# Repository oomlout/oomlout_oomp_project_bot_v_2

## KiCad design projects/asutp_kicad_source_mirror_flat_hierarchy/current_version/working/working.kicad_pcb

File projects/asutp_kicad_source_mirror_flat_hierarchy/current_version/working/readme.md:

# kicad_source_mirror
 
## summary 
* id: asutp_kicad_source_mirror_flat_hierarchy
* user: asutp
* name: kicad_source_mirror
* board: flat_hierarchy
* repo: https://github.com/asutp/kicad-source-mirror
* src_file_repo_kicad_pcb: demos/flat_hierarchy/flat_hierarchy.kicad_pcb
* src_file_repo_kicad_pcb_link: https://github.com/asutp/kicad-source-mirror/tree/master/demos/flat_hierarchy/flat_hierarchy.kicad_pcb

* src_file_repo_sch: demos/flat_hierarchy/flat_hierarchy.sch
* src_file_repo_sch_link: https://github.com/asutp/kicad-source-mirror/tree/master/demos/flat_hierarchy/flat_hierarchy.sch
* full details link: https://github.com/oomlout/oomlout_oomp_project_bot_v_2/tree/main/projects/asutp_kicad_source_mirror_flat_hierarchy/current_version/working  

## pcb  

[board (pdf)](working.pdf)  

## working_bom
| Id | Designator | Footprint | Quantity | Designation | Supplier and ref |  | None | 
| --- | --- | --- | --- | --- | --- | --- | --- | 
| 1 | P3 | 40DIP-ELL600 | 1 | SUPP40 |  |  | [''] | 
| 2 | 1PIN,1PIN,1PIN,1PIN,1PIN,1PIN | 1pin | 6 | P*** |  |  | [''] | 
| 3 | P2 | 28DIP-ELL300 | 1 | SUPP28 |  |  | [''] | 
| 4 | C1 | CP10 | 1 | 100uF |  |  | [''] | 
| 5 | C2 | CP10 | 1 | 220uF |  |  | [''] | 
| 6 | C3 | CP8 | 1 | 22uF/25V |  |  | [''] | 
| 7 | C4 | C1-1 | 1 | 0 |  |  | [''] | 
| 8 | C5 | C1-1 | 1 | 10nF |  |  | [''] | 
| 9 | C6,C7,C8 | C1-1 | 3 | 100nF |  |  | [''] | 
| 10 | C9 | C1-1 | 1 | 22OnF |  |  | [''] | 
| 11 | D1 | D5 | 1 | 1N4004 |  |  | [''] | 
| 12 | D2,D3,D4,D5,D6,D7,D11 | D3 | 7 | BAT43 |  |  | [''] | 
| 13 | D8 | LEDV | 1 | RED-LED |  |  | [''] | 
| 14 | D9 | LEDV | 1 | GREEN-LED |  |  | [''] | 
| 15 | D10 | D5 | 1 | SCHOTTKY |  |  | [''] | 
| 16 | D12 | LEDV | 1 | YELLOW-LED |  |  | [''] | 
| 17 | J1 | DB9FC | 1 | DB9-FEMAL |  |  | [''] | 
| 18 | JP1 | PIN_ARRAY_2X1 | 1 | JUMPER |  |  | [''] | 
| 19 | L1 | INDUCTOR_V | 1 | 22uH |  |  | [''] | 
| 20 | P1 | bornier2 | 1 | CONN_2 |  |  | [''] | 
| 21 | Q1 | TO92 | 1 | BC237 |  |  | [''] | 
| 22 | Q2,Q3 | TO92 | 2 | BC307 |  |  | [''] | 
| 23 | R1,R2,R3,R4,R5,R6,R7 | R4 | 7 | 10K |  |  | [''] | 
| 24 | R8 | R4 | 1 | 1K |  |  | [''] | 
| 25 | R9,R19,R20 | R4 | 3 | 2.2K |  |  | [''] | 
| 26 | R10 | R4 | 1 | 5,1K |  |  | [''] | 
| 27 | R11,R17 | R4 | 2 | 22K |  |  | [''] | 
| 28 | R12,R13,R14,R21 | R4 | 4 | 470 |  |  | [''] | 
| 29 | R15 | R4 | 1 | 6.2K |  |  | [''] | 
| 30 | R16 | R4 | 1 | 62K |  |  | [''] | 
| 31 | R18 | R4 | 1 | 220 |  |  | [''] | 
| 32 | RV1 | RV2X4 | 1 | 1K |  |  | [''] | 
| 33 | U1 | DIP-8__300_ELL | 1 | 24Cxx |  |  | [''] | 
| 34 | U2 | DIP-14__300_ELL | 1 | 74HC125 |  |  | [''] | 
| 35 | U3 | LM78XX | 1 | 7805 |  |  | [''] | 
| 36 | U4 | DIP-8__300_ELL | 1 | LT1373 |  |  | [''] | 
| 37 | U5 | DIP-18__300_ELL | 1 | PIC_18_PINS |  |  | [''] | 
| 38 | U6 | DIP-8__300_ELL | 1 | PIC_8_PINS |  |  | [''] |

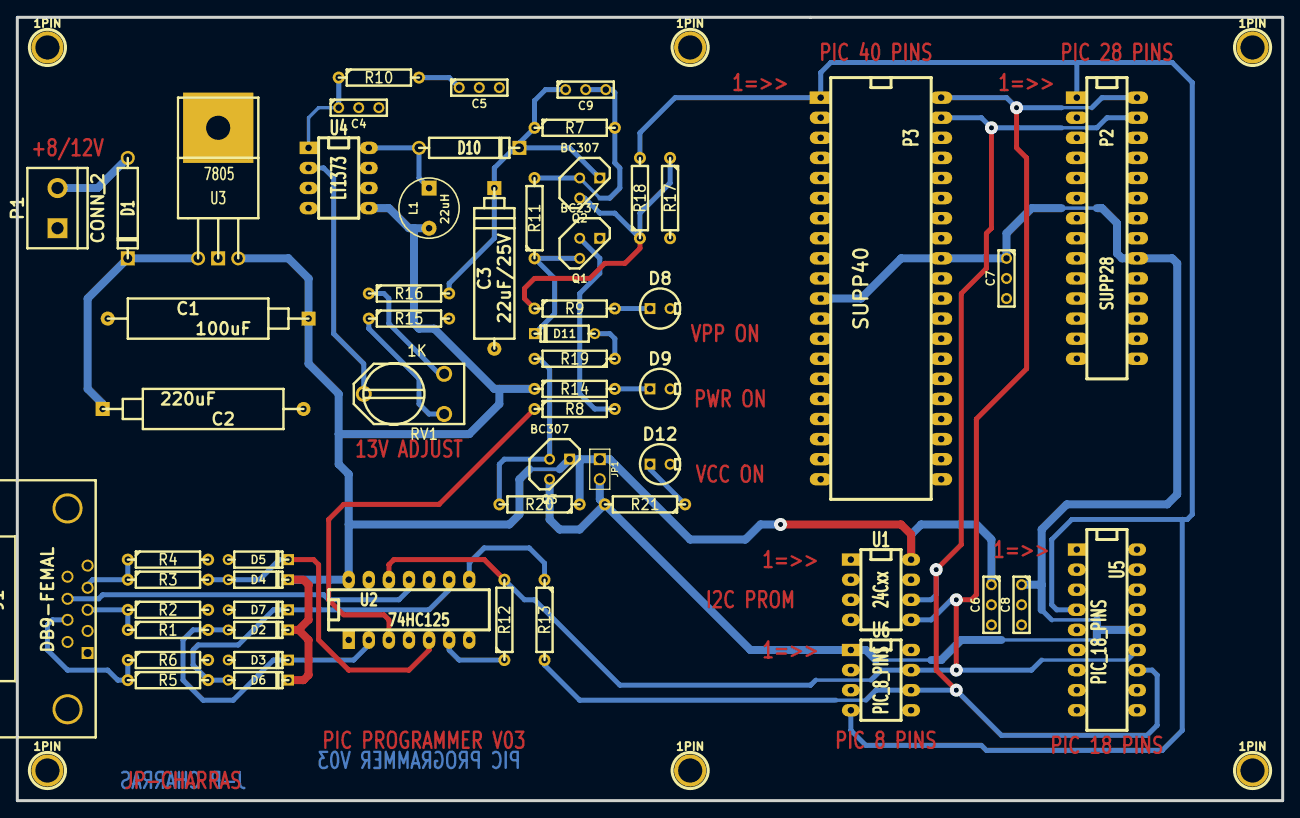
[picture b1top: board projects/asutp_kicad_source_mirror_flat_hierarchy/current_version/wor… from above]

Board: 2 copper layers, 160.0 x 99.1 mm, 64 parts (0 on the bottom side), 34 nets.

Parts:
1PIN, 1PIN#2, 1PIN#3, 1PIN#4, 1PIN#5, 1PIN#6: P***; 1pin
C1: 100uF; CP10
C2: 220uF; CP10
C3: 22uF/25V; CP8
C4: 0; C1-1
C5: 10nF; C1-1
C6, C7, C8: 100nF; C1-1
C9: 22OnF; C1-1
D1: 1N4004; D5
D2, D3, D4, D5, D6, D7, D11: BAT43; D3
D8: RED-LED; LEDV
D9: GREEN-LED; LEDV
D10: SCHOTTKY; D5
D12: YELLOW-LED; LEDV
J1: DB9-FEMAL; DB9FC
JP1: JUMPER; PIN_ARRAY_2X1
L1: 22uH; INDUCTOR_V
P1: CONN_2; bornier2
P2: SUPP28; 28DIP-ELL300
P3: SUPP40; 40DIP-ELL600
Q1: BC237; TO92
Q2, Q3: BC307; TO92
R1, R2, R3, R4, R5, R6, R7: 10K; R4
R8: 1K; R4
R9, R19, R20: 2.2K; R4
R10: 5,1K; R4
R11, R17: 22K; R4
R12, R13, R14, R21: 470; R4
R15: 6.2K; R4
R16: 62K; R4
R18: 220; R4
RV1: 1K; RV2X4
U1: 24Cxx; DIP-8__300_ELL
U2: 74HC125; DIP-14__300_ELL
U3: 7805; LM78XX
U4: LT1373; DIP-8__300_ELL
U5: PIC_18_PINS; DIP-18__300_ELL
U6: PIC_8_PINS; DIP-8__300_ELL

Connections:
/pic_programmer/CTS: J1.8, U2.11
/pic_programmer/DTR: J1.4, R3.1, R4.1
/pic_programmer/PC-CLOCK-OUT: J1.7, R5.1, R6.1
/pic_programmer/TXD: J1.3, R1.1, R2.1
CLOCK-RB6: P2.27, P3.39, R13.2, U1.6, U5.12, U6.6
DATA-RB7: P2.28, P3.40, R12.2, U1.5, U2.12, U5.13, U6.7
GND: C1.2, C2.2, C3.2, C4.2, C5.2, C6.2, C7.2, C8.2, D3.1, D5.1, D7.1, D8.2, D9.2, D12.2, J1.5, P1.1, P2.8, P2.19, P3.8, P3.12, P3.31, Q1.1, R2.2, R4.2, R6.2, R15.2, R17.2, U1.1, U1.2, U1.3, U1.4, U2.1, U2.4, U2.7, U2.10, U2.13, U3.GND, U4.6, U4.7, U5.5, U6.8
unnamed: C2.1, D1.2, U3.VI
unnamed: C4.1, R10.1, U4.1
unnamed: C5.1, R10.2
unnamed: C9.2, Q2.2, R7.2, R11.2
unnamed: D1.1, P1.2
unnamed: D2.1, D3.2, R1.2, U2.2
unnamed: D4.1, D5.2, R3.2, U2.5
unnamed: D6.1, D7.2, R5.2, U2.9
unnamed: D8.1, R9.2
unnamed: D9.1, R14.2
unnamed: D10.1, L1.1, U4.8
unnamed: D11.1, R19.1
unnamed: D11.2, Q1.3, R11.1
unnamed: D12.1, R21.1
unnamed: Q1.2, R8.2
unnamed: Q2.3, R9.1, R17.1, R18.1
unnamed: Q3.2, R19.2, R20.2
unnamed: R8.1, U2.3
unnamed: R12.1, U2.6
unnamed: R13.1, U2.8
unnamed: R15.1, RV1.1
unnamed: R16.1, RV1.3
unnamed: RV1.2, U4.2
VCC: C1.1, C6.1, D2.2, D4.2, D6.2, JP1.1, L1.2, Q3.1, R14.1, R20.1, U1.8, U2.14, U3.VO, U4.5
VCC_PIC: C7.1, C8.1, JP1.2, P2.20, P3.11, P3.32, Q3.3, R21.2, U5.14, U6.1
VPP: C3.1, C9.1, D10.2, Q2.1, R7.1, R16.2
VPP-MCLR: P2.1, P3.1, R18.2, U5.4, U6.4

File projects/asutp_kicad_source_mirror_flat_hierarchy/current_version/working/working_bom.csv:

"Id";"Designator";"Footprint";"Quantity";"Designation";"Supplier and ref";
1;"P3";"40DIP-ELL600";1;"SUPP40";;;
2;"1PIN,1PIN,1PIN,1PIN,1PIN,1PIN";"1pin";6;"P***";;;
3;"P2";"28DIP-ELL300";1;"SUPP28";;;
4;"C1";"CP10";1;"100uF";;;
5;"C2";"CP10";1;"220uF";;;
6;"C3";"CP8";1;"22uF/25V";;;
7;"C4";"C1-1";1;"0";;;
8;"C5";"C1-1";1;"10nF";;;
9;"C6,C7,C8";"C1-1";3;"100nF";;;
10;"C9";"C1-1";1;"22OnF";;;
11;"D1";"D5";1;"1N4004";;;
12;"D2,D3,D4,D5,D6,D7,D11";"D3";7;"BAT43";;;
13;"D8";"LEDV";1;"RED-LED";;;
14;"D9";"LEDV";1;"GREEN-LED";;;
15;"D10";"D5";1;"SCHOTTKY";;;
16;"D12";"LEDV";1;"YELLOW-LED";;;
17;"J1";"DB9FC";1;"DB9-FEMAL";;;
18;"JP1";"PIN_ARRAY_2X1";1;"JUMPER";;;
19;"L1";"INDUCTOR_V";1;"22uH";;;
20;"P1";"bornier2";1;"CONN_2";;;
21;"Q1";"TO92";1;"BC237";;;
22;"Q2,Q3";"TO92";2;"BC307";;;
23;"R1,R2,R3,R4,R5,R6,R7";"R4";7;"10K";;;
24;"R8";"R4";1;"1K";;;
25;"R9,R19,R20";"R4";3;"2.2K";;;
26;"R10";"R4";1;"5,1K";;;
27;"R11,R17";"R4";2;"22K";;;
28;"R12,R13,R14,R21";"R4";4;"470";;;
29;"R15";"R4";1;"6.2K";;;
30;"R16";"R4";1;"62K";;;
31;"R18";"R4";1;"220";;;
32;"RV1";"RV2X4";1;"1K";;;
33;"U1";"DIP-8__300_ELL";1;"24Cxx";;;
34;"U2";"DIP-14__300_ELL";1;"74HC125";;;
35;"U3";"LM78XX";1;"7805";;;
36;"U4";"DIP-8__300_ELL";1;"LT1373";;;
37;"U5";"DIP-18__300_ELL";1;"PIC_18_PINS";;;
38;"U6";"DIP-8__300_ELL";1;"PIC_8_PINS";;;

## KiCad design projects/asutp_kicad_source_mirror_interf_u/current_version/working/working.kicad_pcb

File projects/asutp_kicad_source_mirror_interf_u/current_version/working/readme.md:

# kicad_source_mirror
 
## summary 
* id: asutp_kicad_source_mirror_interf_u
* user: asutp
* name: kicad_source_mirror
* board: interf_u
* repo: https://github.com/asutp/kicad-source-mirror
* src_file_repo_kicad_pcb: demos/interf_u/interf_u.kicad_pcb
* src_file_repo_kicad_pcb_link: https://github.com/asutp/kicad-source-mirror/tree/master/demos/interf_u/interf_u.kicad_pcb

* src_file_repo_sch: demos/interf_u/interf_u.sch
* src_file_repo_sch_link: https://github.com/asutp/kicad-source-mirror/tree/master/demos/interf_u/interf_u.sch
* full details link: https://github.com/oomlout/oomlout_oomp_project_bot_v_2/tree/main/projects/asutp_kicad_source_mirror_interf_u/current_version/working  

## schematic  
  
[schematic (pdf)](working_schematic.pdf) 

## pcb  

[board (pdf)](working.pdf)  

## working_bom
| Id | Designator | Footprint | Quantity | Designation | Supplier and ref |  | None | 
| --- | --- | --- | --- | --- | --- | --- | --- | 
| 1 | BUS1 | BUS_PC | 1 | BUSPC |  |  | [''] | 
| 2 | R4,R5 | R3 | 2 | 330 |  |  | [''] | 
| 3 | D1,D2 | LED-5MM | 2 | LED |  |  | [''] | 
| 4 | U9 | PGA120 | 1 | 4003APG120 |  |  | [''] | 
| 5 | C6,C5,C4,C1 | CP6 | 4 | 47uF |  |  | [''] | 
| 6 | R1 | R3 | 1 | 100K |  |  | [''] | 
| 7 | R2 | R3 | 1 | 1K |  |  | [''] | 
| 8 | X1 | HC-18UH | 1 | 8MHz |  |  | [''] | 
| 9 | C2,C3 | C_Disc_D3_P2.5 | 2 | 47pF |  |  | [''] | 
| 10 | U5 | DIP-32__600 | 1 | 628128 |  |  | [''] | 
| 11 | R3 | R3 | 1 | 10K |  |  | [''] | 
| 12 | P1 | DB25FC | 1 | DB25FEMELLE |  |  | [''] | 
| 13 | RR1 | r_pack9 | 1 | 9x1K |  |  | [''] | 
| 14 | JP1 | Pin_Header_Straight_2x08 | 1 | CONN_8X2 |  |  | [''] | 
| 15 | U1 | DIP-20__300 | 1 | 74LS245 |  |  | [''] | 
| 16 | U2 | DIP-20__300 | 1 | 74LS688 |  |  | [''] | 
| 17 | U3 | DIP-20__300 | 1 | 74LS541 |  |  | [''] | 
| 18 | U8 | DIP-24__300 | 1 | EP600 |  |  | [''] | 
| 19 | G*** | LOGO | 1 | LOGO |  |  | [''] | 

## bom_schematic
| Ref | Qnty | Value | Cmp name | Footprint | Description | Vendor | DNP | 
| --- | --- | --- | --- | --- | --- | --- | --- | 
| BUS1 | 1 | BUSPC | BUSPC | BUS_PC |  |  |  | 
| C1, C4, C5, C6 | 4 | 47uF | CP | Discret:CP6 |  |  |  | 
| C2, C3 | 2 | 47pF | C | Discret:C1 |  |  |  | 
| D1, D2 | 2 | LED | LED | LEDs:LED-5MM |  |  |  | 
| JP1 | 1 | CONN_8X2 | CONN_8X2 | pin_array_8x2 |  |  |  | 
| P1 | 1 | DB25FEMELLE | DB25 | connect:DB25FC |  |  |  | 
| R1 | 1 | 100K | R | Discret:R3 |  |  |  | 
| R2 | 1 | 1K | R | Discret:R3 |  |  |  | 
| R3 | 1 | 10K | R | Discret:R3 |  |  |  | 
| R4, R5 | 2 | 330 | R | Discret:R3 |  |  |  | 
| RR1 | 1 | 9x1K | RR9 | Discret:r_pack9 |  |  |  | 
| U1 | 1 | 74LS245 | 74LS245 | Dip_sockets:DIP-20__300 |  |  |  | 
| U2 | 1 | 74LS688 | 74LS688 | Dip_sockets:DIP-20__300 |  |  |  | 
| U3 | 1 | 74LS541 | 74LS541 | Dip_sockets:DIP-20__300 |  |  |  | 
| U5 | 1 | 628128 | 628128 | Dip_sockets:DIP-32__600 |  |  |  | 
| U8 | 1 | EP600 | EP600 | Dip_sockets:DIP-24__300 |  |  |  | 
| U9 | 1 | 4003APG120 | 4003APG120 | Sockets_PGA:PGA120 |  |  |  | 
| X1 | 1 | 8MHz | CRYSTAL | Discret:HC-18UH |  |  |  |

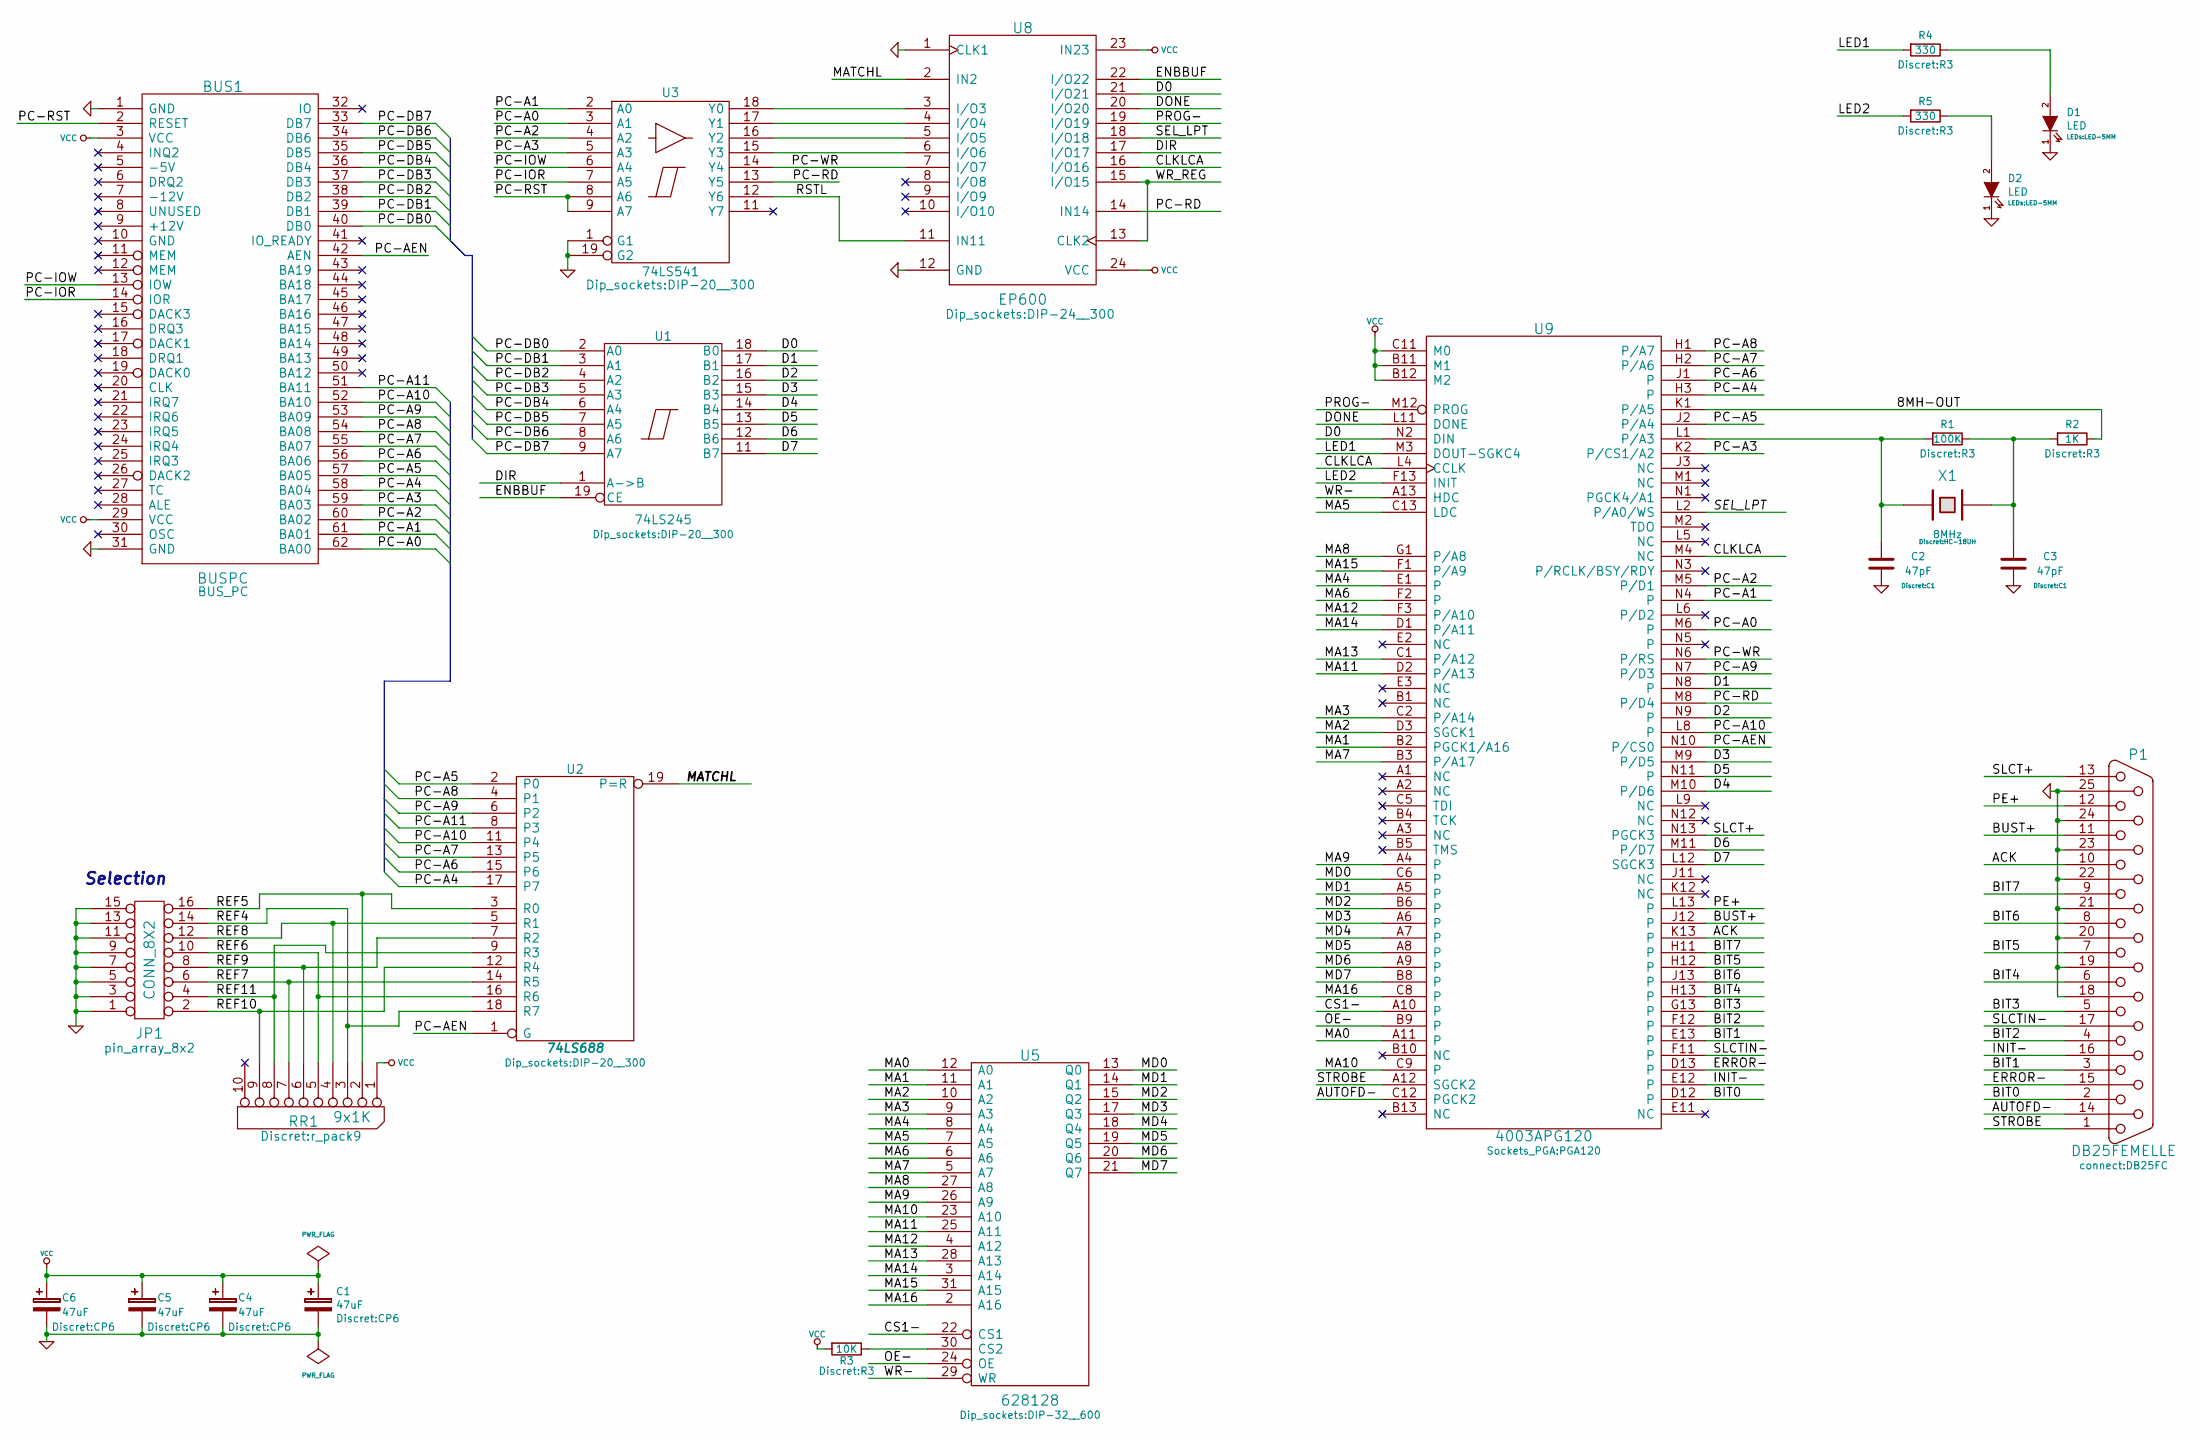
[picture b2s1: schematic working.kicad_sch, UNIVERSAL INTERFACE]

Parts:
BUS1: BUSPC; BUS_PC
C1, C4, C5, C6: 47uF; CP6
C2, C3: 47pF; C1
D1, D2: LED; LED-5MM
JP1: CONN_8X2; pin_array_8x2
P1: DB25FEMELLE; DB25FC
R1: 100K; R3
R2: 1K; R3
R3: 10K; R3
R4, R5: 330; R3
RR1: 9x1K; r_pack9
U1: 74LS245; DIP-20__300
U2: 74LS688; DIP-20__300
U3: 74LS541; DIP-20__300
U5: 628128; DIP-32__600
U8: EP600; DIP-24__300
U9: 4003APG120; PGA120
X1: 8MHz; HC-18UH

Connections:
/8MH-OUT: R2.1, U9.K1 (P/A5)
/ACK: P1.10, U9.K13
/AUTOFD-: P1.14, U9.C12 (PGCK2)
/BIT0: P1.2, U9.D12
/BIT1: P1.3, U9.E13
/BIT2: P1.4, U9.F12
/BIT3: P1.5, U9.G13
/BIT4: P1.6, U9.H13
/BIT5: P1.7, U9.H12
/BIT6: P1.8, U9.J13
/BIT7: P1.9, U9.H11
/BUST+: P1.11, U9.J12
/CLKLCA: U8.16 (I/O16), U9.L4 (CCLK), U9.M4 (NC)
/CS1-: U5.22 (CS1), U9.A10
/D0: U1.18 (B0), U8.21 (I/O21), U9.N2 (DIN)
/D1: U1.17 (B1), U9.N8
/D2: U1.16 (B2), U9.N9
/D3: U1.15 (B3), U9.M9 (P/D5)
/D4: U1.14 (B4), U9.M10 (P/D6)
/D5: U1.13 (B5), U9.N11
/D6: U1.12 (B6), U9.M11 (P/D7)
/D7: U1.11 (B7), U9.L12 (SGCK3)
/DIR: U1.1 (A->B), U8.17 (I/O17)
/DONE: U8.20 (I/O20), U9.L11 (DONE)
/ENBBUF: U1.19 (CE), U8.22 (I/O22)
/ERROR-: P1.15, U9.D13
/INIT-: P1.16, U9.E12
/LED1: R4.2, U9.M3 (DOUT-SGKC4)
/LED2: R5.2, U9.F13 (INIT)
/MA0: U5.12 (A0), U9.A11
/MA1: U5.11 (A1), U9.B2 (PGCK1/A16)
/MA2: U5.10 (A2), U9.D3 (SGCK1)
/MA3: U5.9 (A3), U9.C2 (P/A14)
/MA4: U5.8 (A4), U9.E1
/MA5: U5.7 (A5), U9.C13 (LDC)
/MA6: U5.6 (A6), U9.F2
/MA7: U5.5 (A7), U9.B3 (P/A17)
/MA8: U5.27 (A8), U9.G1 (P/A8)
/MA9: U5.26 (A9), U9.A4
/MA10: U5.23 (A10), U9.C9
/MA11: U5.25 (A11), U9.D2 (P/A13)
/MA12: U5.4 (A12), U9.F3 (P/A10)
/MA13: U5.28 (A13), U9.C1 (P/A12)
/MA14: U5.3 (A14), U9.D1 (P/A11)
/MA15: U5.31 (A15), U9.F1 (P/A9)
/MA16: U5.2 (A16), U9.C8
/MATCHL: U2.19 (P=R), U8.2 (IN2)
/MD0: U5.13 (Q0), U9.C6
/MD1: U5.14 (Q1), U9.A5
/MD2: U5.15 (Q2), U9.B6
/MD3: U5.17 (Q3), U9.A6
/MD4: U5.18 (Q4), U9.A7
/MD5: U5.19 (Q5), U9.A8
/MD6: U5.20 (Q6), U9.A9
/MD7: U5.21 (Q7), U9.B8
/OE-: U5.24 (OE), U9.B9
/PC-A0: BUS1.62 (BA00), U3.3 (A1), U9.M6
/PC-A1: BUS1.61 (BA01), U3.2 (A0), U9.N4
/PC-A2: BUS1.60 (BA02), U3.4 (A2), U9.M5 (P/D1)
/PC-A3: BUS1.59 (BA03), U3.5 (A3), U9.K2 (P/CS1/A2)
/PC-A4: BUS1.58 (BA04), U2.17 (P7), U9.H3
/PC-A5: BUS1.57 (BA05), U2.2 (P0), U9.J2 (P/A4)
/PC-A6: BUS1.56 (BA06), U2.15 (P6), U9.J1
/PC-A7: BUS1.55 (BA07), U2.13 (P5), U9.H2 (P/A6)
/PC-A8: BUS1.54 (BA08), U2.4 (P1), U9.H1 (P/A7)
/PC-A9: BUS1.53 (BA09), U2.6 (P2), U9.N7 (P/D3)
/PC-A10: BUS1.52 (BA10), U2.11 (P4), U9.L8
/PC-A11: BUS1.51 (BA11), U2.8 (P3)
/PC-AEN: BUS1.42 (AEN), U2.1 (G), U9.N10 (P/CS0)
/PC-DB0: BUS1.40 (DB0), U1.2 (A0)
/PC-DB1: BUS1.39 (DB1), U1.3 (A1)
/PC-DB2: BUS1.38 (DB2), U1.4 (A2)
/PC-DB3: BUS1.37 (DB3), U1.5 (A3)
/PC-DB4: BUS1.36 (DB4), U1.6 (A4)
/PC-DB5: BUS1.35 (DB5), U1.7 (A5)
/PC-DB6: BUS1.34 (DB6), U1.8 (A6)
/PC-DB7: BUS1.33 (DB7), U1.9 (A7)
/PC-IOR: BUS1.14 (IOR), U3.7 (A5)
/PC-IOW: BUS1.13 (IOW), U3.6 (A4)
/PC-RD: U3.13 (Y5), U8.14 (IN14), U9.M8 (P/D4)
/PC-RST: BUS1.2 (RESET), U3.8 (A6), U3.9 (A7)
/PC-WR: U3.14 (Y4), U8.7 (I/O7), U9.N6 (P/RS)
/PE+: P1.12, U9.L13
/PROG-: U8.19 (I/O19), U9.M12 (PROG)
/REF4: JP1.14, RR1.3, U2.18 (R7)
/REF5: JP1.16, RR1.2, U2.3 (R0)
/REF6: JP1.10, RR1.5, U2.16 (R6)
/REF7: JP1.6, RR1.7, U2.14 (R5)
/REF8: JP1.12, RR1.4, U2.5 (R1)
/REF9: JP1.8, RR1.6, U2.7 (R2)
/REF10: JP1.2, RR1.9, U2.12 (R4)
/REF11: JP1.4, RR1.8, U2.9 (R3)
/RSTL: U3.12 (Y6), U8.11 (IN11)
/SEL_LPT: U8.18 (I/O18), U9.L2 (P/A0/WS)
/SLCT+: P1.13, U9.N13 (PGCK3)
/SLCTIN-: P1.17, U9.F11
/STROBE: P1.1, U9.A12 (SGCK2)
/WR-: U5.29 (WR), U9.A13 (HDC)
/WR_REG: U8.13 (CLK2), U8.15 (I/O15)
GND: BUS1.1 (GND), BUS1.31 (GND), C1.2, C2.2, C3.2, C4.2, C5.2, C6.2, D1.1 (K), D2.1 (K), JP1.1, JP1.3, JP1.5, JP1.7, JP1.9, JP1.11, JP1.13, JP1.15, P1.18, P1.19, P1.20, P1.21, P1.22, P1.23, P1.24, P1.25, U1.10 (GND), U2.10 (GND), U3.1 (G1), U3.10 (GND), U3.19 (G2), U5.16 (GND), U8.1 (CLK1), U8.12 (GND), U9.B7 (GND), U9.C4 (GND), U9.C10 (GND), U9.G2 (GND), U9.G11 (GND), U9.K3 (GND), U9.K11 (GND), U9.L7 (GND)
unnamed: C2.1, R1.2, U9.L1 (P/A3), X1.1
unnamed: C3.1, R1.1, R2.2, X1.2
unnamed: D1.2 (A), R4.1
unnamed: D2.2 (A), R5.1
unnamed: R3.1, U5.30 (CS2)
unnamed: U3.15 (Y3), U8.6 (I/O6)
unnamed: U3.16 (Y2), U8.5 (I/O5)
unnamed: U3.17 (Y1), U8.4 (I/O4)
unnamed: U3.18 (Y0), U8.3 (I/O3)
VCC: BUS1.3 (VCC), BUS1.29 (VCC), C1.1, C4.1, C5.1, C6.1, R3.2, RR1.1 (COM), U1.20 (VCC), U2.20 (VCC), U3.20 (VCC), U5.32 (VCC), U8.23 (IN23), U8.24 (VCC), U9.B11 (M1), U9.B12 (M2), U9.C3 (VCC), U9.C11 (M0), U9.D11 (VCC), U9.G12 (VCC), U9.L3 (VCC), U9.L10 (VCC), U9.M7 (VCC)

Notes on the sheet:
Selection

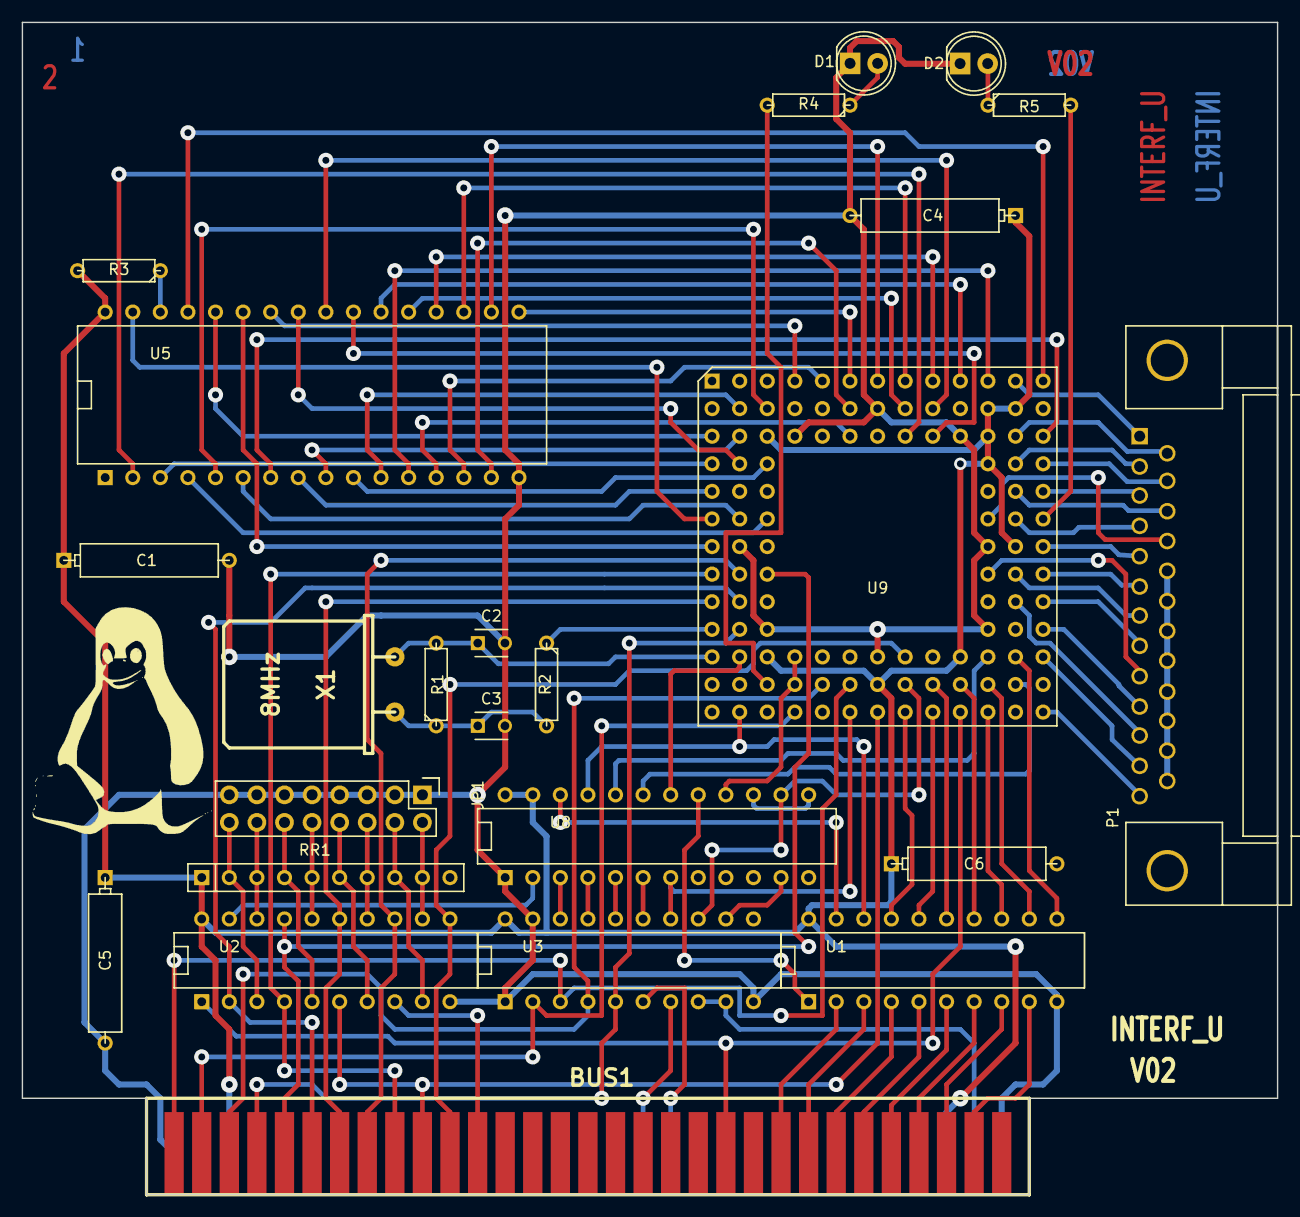
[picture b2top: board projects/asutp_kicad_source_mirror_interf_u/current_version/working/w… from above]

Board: 2 copper layers, 115.6 x 108.0 mm, 24 parts (0 on the bottom side), 110 nets.

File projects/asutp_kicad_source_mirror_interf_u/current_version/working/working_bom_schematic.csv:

"Source:","C:\gh\oomlout_oomp_project_bot_v_2\projects\asutp_kicad_source_mirror_interf_u\current_version\working\working.kicad_sch"
"Date:","26/09/2023 19:25:04"
"Tool:","Eeschema 7.0.6"
"Generator:","C:/Program Files/KiCad/7.0/bin/scripting/plugins/bom_csv_grouped_by_value_with_fp.py"
"Component Count:","24"
"Ref","Qnty","Value","Cmp name","Footprint","Description","Vendor","DNP"
"BUS1","1","BUSPC","BUSPC","BUS_PC","","",""
"C1, C4, C5, C6","4","47uF","CP","Discret:CP6","","",""
"C2, C3","2","47pF","C","Discret:C1","","",""
"D1, D2","2","LED","LED","LEDs:LED-5MM","","",""
"JP1","1","CONN_8X2","CONN_8X2","pin_array_8x2","","",""
"P1","1","DB25FEMELLE","DB25","connect:DB25FC","","",""
"R1","1","100K","R","Discret:R3","","",""
"R2","1","1K","R","Discret:R3","","",""
"R3","1","10K","R","Discret:R3","","",""
"R4, R5","2","330","R","Discret:R3","","",""
"RR1","1","9x1K","RR9","Discret:r_pack9","","",""
"U1","1","74LS245","74LS245","Dip_sockets:DIP-20__300","","",""
"U2","1","74LS688","74LS688","Dip_sockets:DIP-20__300","","",""
"U3","1","74LS541","74LS541","Dip_sockets:DIP-20__300","","",""
"U5","1","628128","628128","Dip_sockets:DIP-32__600","","",""
"U8","1","EP600","EP600","Dip_sockets:DIP-24__300","","",""
"U9","1","4003APG120","4003APG120","Sockets_PGA:PGA120","","",""
"X1","1","8MHz","CRYSTAL","Discret:HC-18UH","","",""
